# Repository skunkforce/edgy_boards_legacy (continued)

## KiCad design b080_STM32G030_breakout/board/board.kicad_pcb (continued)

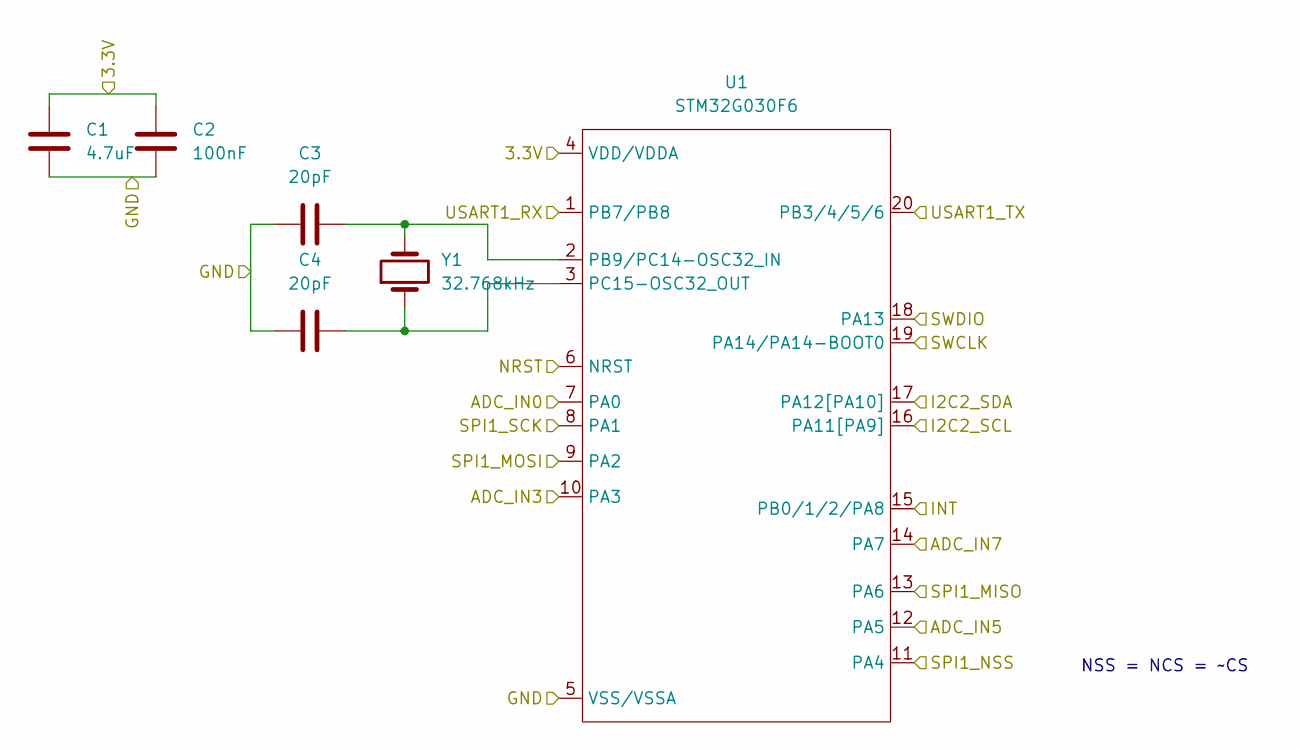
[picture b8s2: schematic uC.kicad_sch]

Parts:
C1: 4.7uF; C_0603_1608Metric_Pad1.08x0.95mm_HandSolder
C2: 100nF; C_0603_1608Metric_Pad1.08x0.95mm_HandSolder
C3, C4: 20pF; C_0603_1608Metric_Pad1.08x0.95mm_HandSolder
U1: STM32G030F6; TSSOP-20_4.4x6.5mm_P0.65mm
Y1: 32.768kHz; Crystal_SMD_5032-2Pin_5.0x3.2mm_HandSoldering; MPN ABS06-32.768KHZ-9-1-T

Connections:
+3V3: C1.1, C2.1, U1.4 (VDD/VDDA); also elsewhere on the board
/uC/ADC_IN0: U1.7 (PA0); also elsewhere on the board
/uC/ADC_IN3: U1.10 (PA3); also elsewhere on the board
/uC/ADC_IN5: U1.12 (PA5); also elsewhere on the board
/uC/ADC_IN7: U1.14 (PA7); also elsewhere on the board
/uC/I2C2_SCL: U1.16 (PA11[PA9]); also elsewhere on the board
/uC/I2C2_SDA: U1.17 (PA12[PA10]); also elsewhere on the board
/uC/INT: U1.15 (PB0/1/2/PA8); also elsewhere on the board
/uC/NRST: U1.6 (NRST); also elsewhere on the board
/uC/SPI1_MISO: U1.13 (PA6); also elsewhere on the board
/uC/SPI1_MOSI: U1.9 (PA2); also elsewhere on the board
/uC/SPI1_NSS: U1.11 (PA4); also elsewhere on the board
/uC/SPI1_SCK: U1.8 (PA1); also elsewhere on the board
/uC/SWCLK: U1.19 (PA14/PA14-BOOT0); also elsewhere on the board
/uC/SWDIO: U1.18 (PA13); also elsewhere on the board
/uC/USART1_RX: U1.1 (PB7/PB8); also elsewhere on the board
/uC/USART1_TX: U1.20 (PB3/4/5/6); also elsewhere on the board
GND: C1.2, C2.2, C3.1, C4.1, U1.5 (VSS/VSSA); also elsewhere on the board
unnamed: C3.2, U1.2 (PB9/PC14-OSC32_IN), Y1.2
unnamed: C4.2, U1.3 (PC15-OSC32_OUT), Y1.1

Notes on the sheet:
NSS = NCS = ~CS

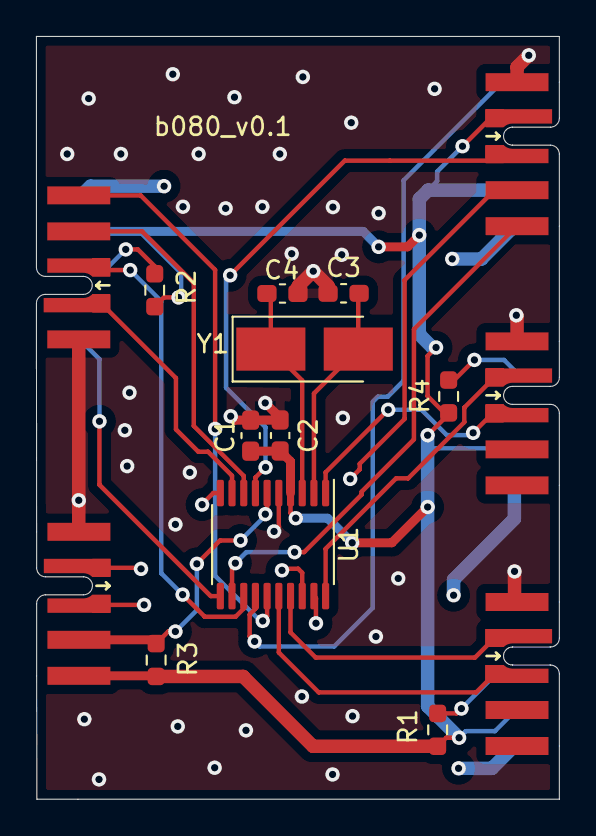
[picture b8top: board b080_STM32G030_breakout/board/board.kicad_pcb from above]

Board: 4 copper layers, 29.1 x 42.4 mm, 15 parts (0 on the bottom side), 24 nets.
